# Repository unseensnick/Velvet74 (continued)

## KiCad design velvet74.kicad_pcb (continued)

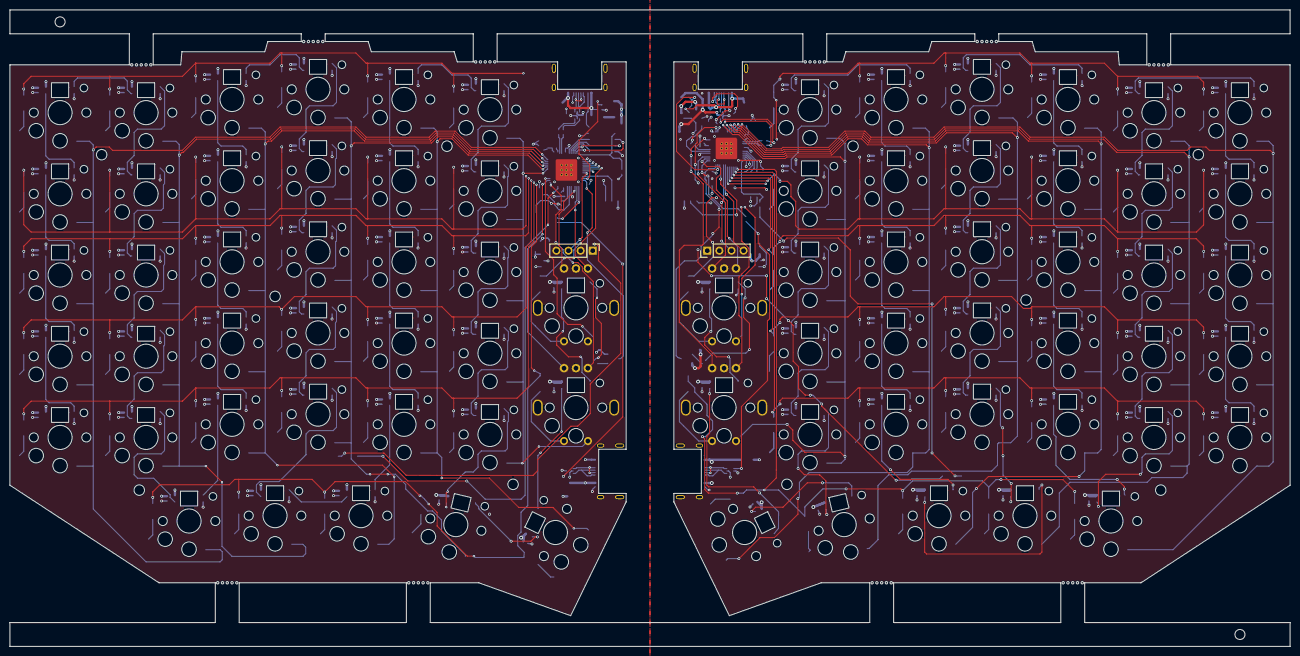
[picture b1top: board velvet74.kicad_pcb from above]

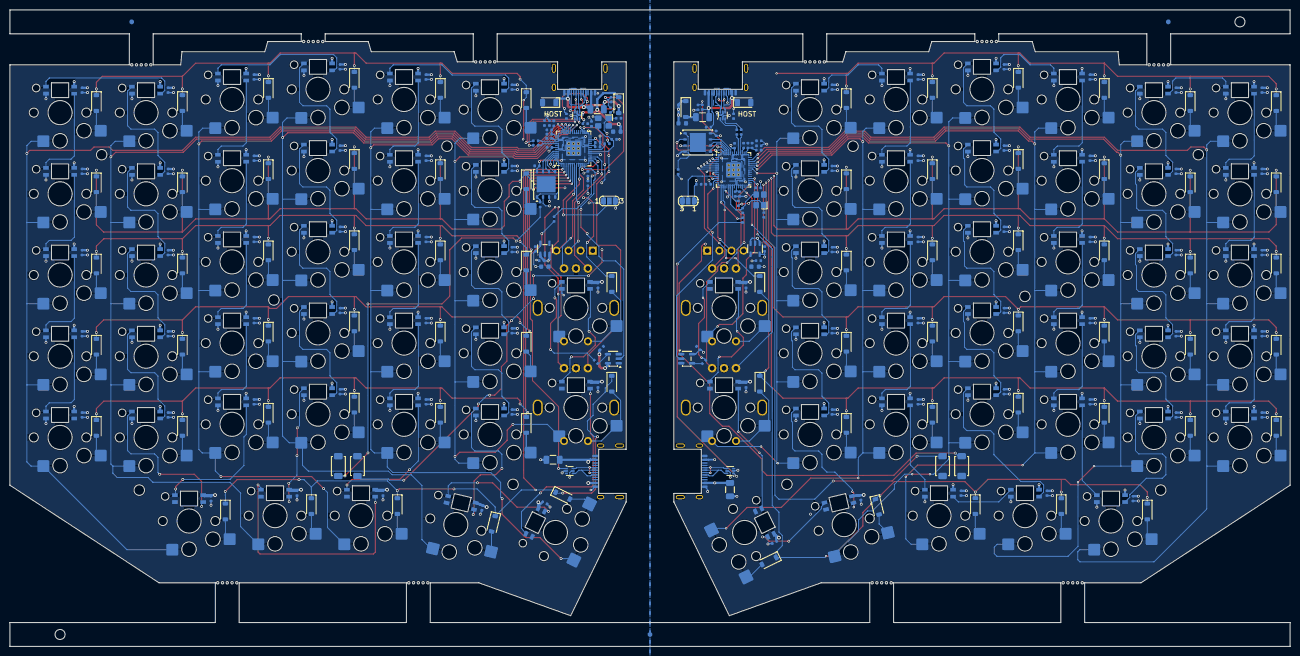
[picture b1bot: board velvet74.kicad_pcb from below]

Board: 4 copper layers, 268.0 x 133.2 mm, 415 parts (317 on the bottom side), 248 nets.

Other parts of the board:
FID1, FID2, FID3: Fiducial_1mm_Mask2mm
MB1, MB2, MB3, MB4, MB5, MB6, MB7, MB8, MB9, MB10: MouseBite_5x0.5mm_P1mm
TH1, TH2: MountingHole_2.1mm

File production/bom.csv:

Designator,Footprint,Quantity,Value,LCSC Part #
"C1, C201, C204, C4",C_0402,4,15pF,C1548
"C10, C11, C110, C111, C112, C113, C114, C115, C116, C12, C120, C121, C122, C123, C124, C125, C13, C130, C131, C132, C133, C134, C135, C14, C140, C141, C142, C143, C144, C145, C15, C150, C151, C152, C153, C154, C155, C16, C160, C161, C162, C163, C164, C165, C17, C203, C205, C206, C210, C211, C212, C213, C214, C215, C216, C217, C230, C3, C30, C310, C311, C312, C313, C314, C315, C316, C320, C321, C322, C323, C324, C325, C330, C331, C332, C333, C334, C335, C340, C341, C342, C343, C344, C345, C350, C351, C352, C353, C354, C355, C360, C361, C362, C363, C364, C365, C5, C6",C_0402,98,100nF,C1525
"C18, C209, C218, C9",C_0603,4,10uF,C19702
"C19, C20, C207, C208, C219, C220, C7, C8",C_0402,8,1uF,C52923
"D1, D201",D_SOD-123,2,B5819W SL,C8598
"D10, D11, D12, D13, D14, D15, D16, D20, D21, D210, D211, D212, D213, D214, D215, D216, D22, D220, D221, D222, D223, D224, D225, D23, D230, D231, D232, D233, D234, D235, D24, D240, D241, D242, D243, D244, D245, D25, D250, D251, D252, D253, D254, D255, D260, D261, D262, D263, D264, D265, D30, D31, D32, D33, D34, D35, D40, D41, D42, D43, D44, D45, D50, D51, D52, D53, D54, D55, D60, D61, D62, D63, D64, D65",D_SOD-123,74,1N4148W,C81598
"D2, D202",D_SOD-123FL,2,SMF5.0A,C19077497
"F1, F2, F201, F202",1206,4,1.1A,C126818
"J1, J2, J201, J202",USB_C_Receptacle_HongCheng_HC-TYPE-C-16P_MidMount,4,"Connector, USB-TYPE-C-16P",C19274022
"LED10, LED11, LED12, LED13, LED14, LED15, LED16, LED20, LED21, LED210, LED211, LED212, LED213, LED214, LED215, LED216, LED22, LED220, LED221, LED222, LED223, LED224, LED225, LED23, LED230, LED231, LED232, LED233, LED234, LED235, LED24, LED240, LED241, LED242, LED243, LED244, LED245, LED25, LED250, LED251, LED252, LED253, LED254, LED255, LED260, LED261, LED262, LED263, LED264, LED265, LED30, LED31, LED32, LED33, LED34, LED35, LED40, LED41, LED42, LED43, LED44, LED45, LED50, LED51, LED52, LED53, LED54, LED55, LED60, LED61, LED62, LED63, LED64, LED65",LED-SMD_4P-L3.2-W2.8-LS5.9_SK6812MINI-E,74,SK6812MINI-E,C5149201
"R10, R11, R210, R211",R_0402,4,10kΩ,C25744
"R15, R215",R_0402,2,470Ω,C25117
"R16, R216",R_0402,2,120Ω,C25079
"R2, R202, R204, R4",R_0402,4,1kΩ,C11702
"R205, R206, R5, R6",R_0402,4,5.1kΩ,C25905
"R207, R208, R7, R8",R_0402,4,27Ω,C25100
"SW1, SW201",SW_Push_1P1T_XUNPU_TS-1088-AR02016,2,BOOT,C720477
"SW2, SW202",SW_Push_1P1T_XUNPU_TS-1088-AR02016,2,RESET,C720477
"U1, U201",QFN-56-1EP_7x7mm_P0.4mm_EP3.2x3.2mm_ThermalVias,2,RP2040,C2040
"U2, U202, U204, U4",SOT-563_USBLC6-2P6,4,USBLC6-2P6,C49451919
"U203, U3",WSON-8-1EP_6x5mm_P1.27mm_EP3.4x4mm,2,ZD25Q128CWIGR,C53959302
"U205, U5",SOT-23-5_L3.0-W1.7-P0.95-LS2.8-BL,2,AP2112K-3.3,C51118
"U206, U6",SOT-23-5,2,SN74LV1T34DBVR,C100024
"X1, X201",CRYSTAL-SMD_4P-L3.2-W2.5-BL,2,ABM8-272-T3,C20625731
